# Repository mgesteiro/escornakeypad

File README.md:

# Escornabot keypad
My own implementation of a keypad for the [Escornabot](https://escornabot.org) educational bot. Firstly created in May-2018 has now been updated, improved and published.

An opensource hardware project developed with and opensource EDA: [KiCAD EDA 5.1](https://www.kicad.org/)

## Manufacturing
If you just want to get your PCBs done, use the [gerber file](gerber.zip) with any of the PCB manufactures around the globe like:

* [JLCPcb](https://jlcpcb.com) (note that my PCB has already markings for this provider)
* [PCBWay](https://pcbway.com)
* [OSHPark](https://oshpark.com)
* [many, many others ...](https://duckduckgo.com/?q=pcb+manufacturers)

**NOTE:** approximate board dimensions 48 x 46 mm, 2 layers, 1.6 mm thickness 

## Fritzing
There's available a [fritzing part](https://github.com/mgesteiro/fritzing-parts/tree/main/EscornaKeypad) for this design:

## LICENSE
This work describes Open Hardware and is licensed under the [CERN-OHL-S v2 license](LICENSE_CERNSV20). It is distributed WITHOUT ANY EXPRESS OR IMPLIED WARRANTY, INCLUDING OF MERCHANTABILITY, SATISFACTORY QUALITY AND FITNESS FOR A PARTICULAR PURPOSE. Please see the [CERN-OHL-S v2](https://ohwr.org/cern_ohl_s_v2.txt) for applicable conditions.

All media and data files that are not part of the hardware design are licensed under the [Creative Commons Attribution 4.0 BY-SA license](LICENSE-CCBYSA40).

More information about licenses in [CERN openhardware licenses](https://ohwr.org/project/cernohl/wikis/Documents/CERN-OHL-version-2), [Opensource licenses](https://opensource.org/licenses/) and [Creative Commons licenses](https://creativecommons.org/licenses/).

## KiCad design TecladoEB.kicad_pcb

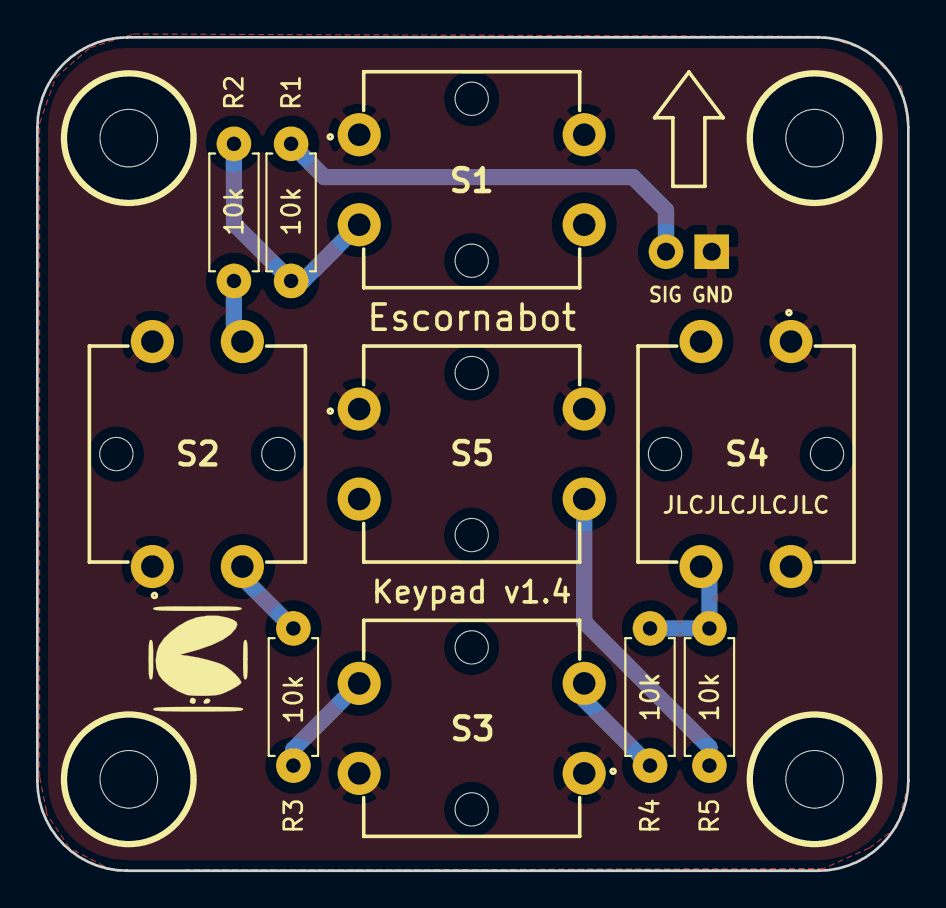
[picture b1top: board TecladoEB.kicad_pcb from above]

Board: 2 copper layers, 48.4 x 46.3 mm, 11 parts (1 on the bottom side), 7 nets.

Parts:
J1: GND SIG; PinHeader_1x02_P2.54mm_Horizontal
R1, R2, R3, R4, R5: 10k; R_Axial_DIN0207_L6.3mm_D2.5mm_P7.62mm_Horizontal_10k
S1, S2, S3, S4, S5: B3F-4055; B3F-4050

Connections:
GND: J1.1, S1.1, S1.2, S2.1, S2.2, S3.1, S3.2, S4.1, S4.2, S5.1, S5.2
unnamed: J1.2, R1.2
unnamed: R1.1, R2.2, S1.3, S1.4
unnamed: R2.1, R3.2, S2.3, S2.4
unnamed: R3.1, R4.2, S3.3, S3.4
unnamed: R4.1, R5.2, S4.3, S4.4
unnamed: R5.1, S5.3, S5.4

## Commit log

2021-05-19 Initial release
2021-05-21 Updated to v1.3, including new LICENSE
2021-05-22 v1.3 Make KiCadStepUp happy and minor cosmetic changes
2021-05-25 Added link to fritzing part
2021-06-02 update gitignore
2022-02-23 Updated to v1.4 with bigger pads
2022-04-14 Updated schematic and images. Exported schematic in SVG.
